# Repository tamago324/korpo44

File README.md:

# korpo44

自分のために設計したキーボード

## v0.1

* [ファームウェア](https://github.com/tamago324/qmk_firmware/tree/71478cf00b8fcf8471fbebe3c2017ffe0b02c1be/keyboards/korpo44)
* [Remap 用ファームウェア](./v0.1/via/korpo44_via.hex)

## ~v0.3~

* これは試しに作っただけだから、発注もしていない
  * でも、一応おいておく

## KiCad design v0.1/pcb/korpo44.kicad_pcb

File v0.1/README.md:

# v0.1

* pcb/
  * PCB
* bottom_plate/
  * ボトムプレート
* top_plate/
  * トッププレート

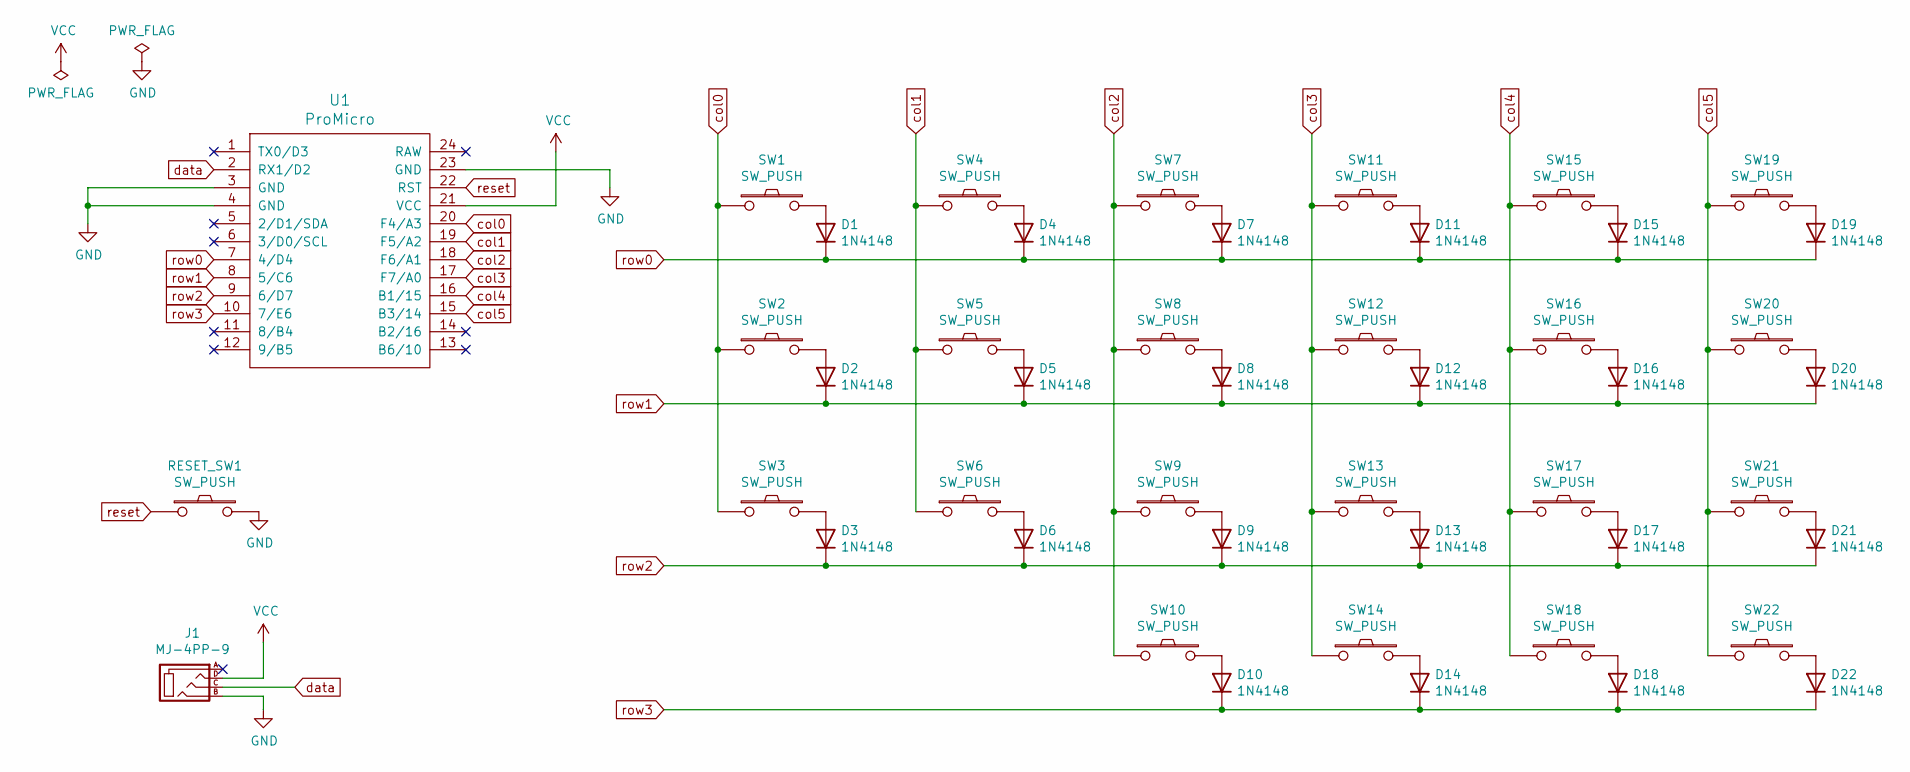
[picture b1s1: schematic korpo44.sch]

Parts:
D1, D2, D3, D4, D5, D6, D7, D8, D9, D10, D11, D12, D13, D14, D15, D16, D17, D18, D19, D20, D21, D22: 1N4148; D3_SMD_v2
J1: MJ-4PP-9
RESET_SW1: SW_PUSH; ResetSW
SW1, SW2, SW3, SW4, SW5, SW6, SW7, SW8, SW9, SW10, SW11, SW12, SW13, SW15, SW16, SW17, SW18, SW19, SW20, SW21, SW22: SW_PUSH; CherryMX_MidHeight_Hotswap
SW14: SW_PUSH; korplone_CherryMX_MidHeight_Hotswap
U1: ProMicro; ProMicro_v2

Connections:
GND: J1.B, RESET_SW1.2, U1.3 (GND), U1.4 (GND), U1.23 (GND)
unnamed: D1.2 (A), SW1.2
unnamed: D2.2 (A), SW2.2
unnamed: D3.2 (A), SW3.2
unnamed: D4.2 (A), SW4.2
unnamed: D5.2 (A), SW5.2
unnamed: D6.2 (A), SW6.2
unnamed: D7.2 (A), SW7.2
unnamed: D8.2 (A), SW8.2
unnamed: D9.2 (A), SW9.2
unnamed: D10.2 (A), SW10.2
unnamed: D11.2 (A), SW11.2
unnamed: D12.2 (A), SW12.2
unnamed: D13.2 (A), SW13.2
unnamed: D14.2 (A), SW14.2
unnamed: D15.2 (A), SW15.2
unnamed: D16.2 (A), SW16.2
unnamed: D17.2 (A), SW17.2
unnamed: D18.2 (A), SW18.2
unnamed: D19.2 (A), SW19.2
unnamed: D20.2 (A), SW20.2
unnamed: D21.2 (A), SW21.2
unnamed: D22.2 (A), SW22.2
VCC: J1.D, U1.21 (VCC)
col0: SW1.1, SW2.1, SW3.1, U1.20 (F4/A3)
col1: SW4.1, SW5.1, SW6.1, U1.19 (F5/A2)
col2: SW7.1, SW8.1, SW9.1, SW10.1, U1.18 (F6/A1)
col3: SW11.1, SW12.1, SW13.1, SW14.1, U1.17 (F7/A0)
col4: SW15.1, SW16.1, SW17.1, SW18.1, U1.16 (B1/15)
col5: SW19.1, SW20.1, SW21.1, SW22.1, U1.15 (B3/14)
data: J1.C, U1.2 (RX1/D2)
reset: RESET_SW1.1, U1.22 (RST)
row0: D1.1 (K), D4.1 (K), D7.1 (K), D11.1 (K), D15.1 (K), D19.1 (K), U1.7 (4/D4)
row1: D2.1 (K), D5.1 (K), D8.1 (K), D12.1 (K), D16.1 (K), D20.1 (K), U1.8 (5/C6)
row2: D3.1 (K), D6.1 (K), D9.1 (K), D13.1 (K), D17.1 (K), D21.1 (K), U1.9 (6/D7)
row3: D10.1 (K), D14.1 (K), D18.1 (K), D22.1 (K), U1.10 (7/E6)

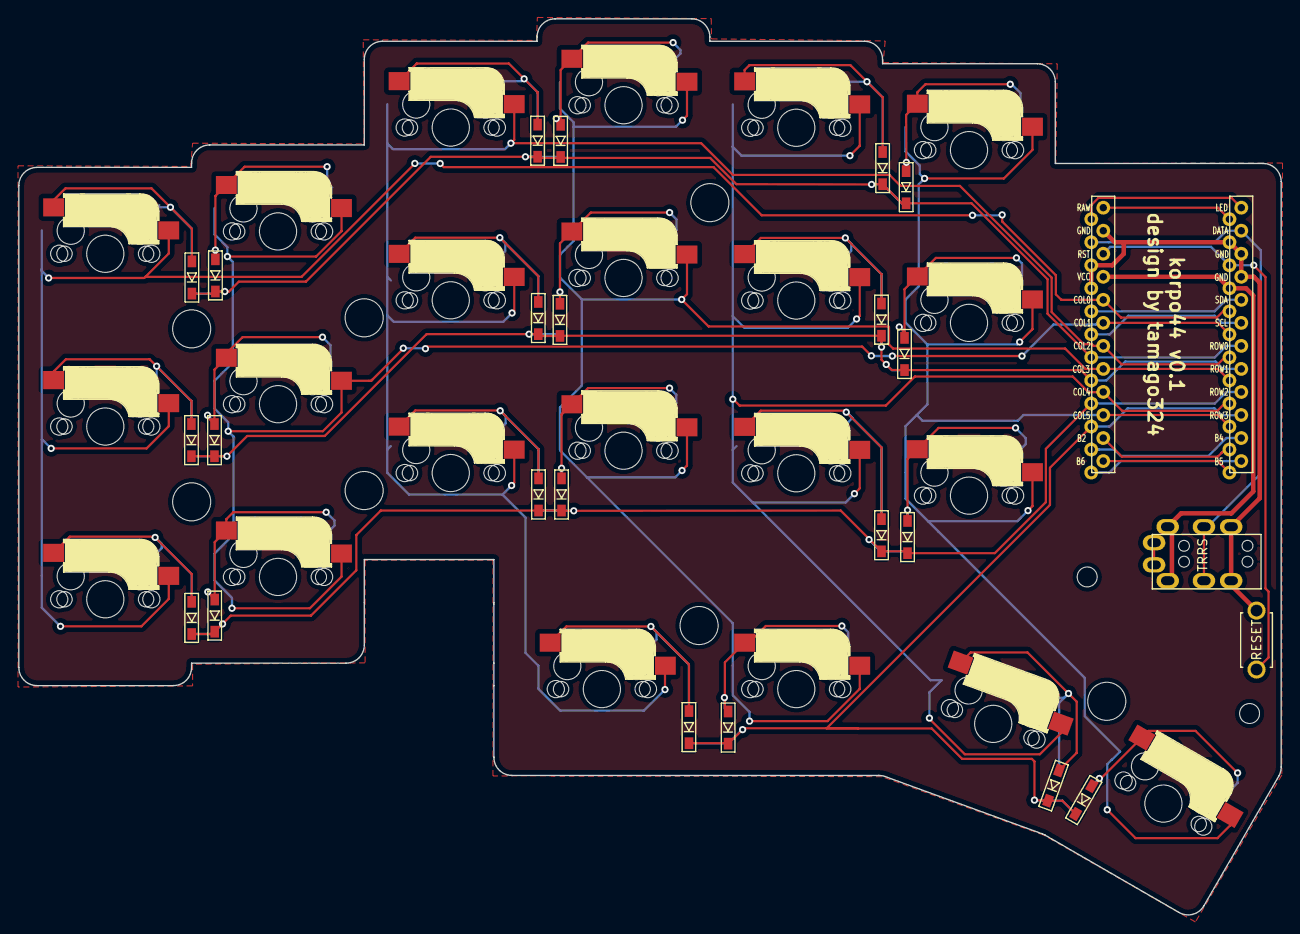
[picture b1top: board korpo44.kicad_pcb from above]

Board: 2 copper layers, 139.2 x 98.8 mm, 56 parts (0 on the bottom side), 36 nets.

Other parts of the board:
Ref**: Val**; M2_HOLE_v2
Ref**#2: Val**; M2_HOLE_v2
Ref**#3, Ref**#4, Ref**#5, Ref**#6, Ref**#7, Ref**#8, Ref**#9: Val**; spacer_m2

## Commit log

2021-08-30 v0.3
2021-09-02 いろいろ整備
2021-09-02 エラー修正
2021-09-02 画像を追加
2021-09-02 fix link
2021-09-02 README.md を修正
2021-09-03 Add LICENSE
2021-09-03 v0.1 の README を更新
2021-09-03 VIA の JSON ファイ雨の名前を変更
